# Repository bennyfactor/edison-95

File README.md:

HP 95LX Block for Intel Edison - Battery/Serial
=================================================

Based on the [SparkFun Block for Intel Edison - Battery/Power (DEV-13037)](https://www.sparkfun.com/products/13037)
and the reference design for the [MAX3218 low voltage TTL-RS232 transciever](https://datasheets.maximintegrated.com/en/ds/MAX3218.pdf)

This block or daughterboard, or whatever, is designed to fit in to the physical dimensions of the HP 95LX palmtop computer's
proto-PCMCIA slot. It has connections for two UARTs (the Edison's console out, and COM1?) that will allow either one to be connected to the HP95LX's serial header.
It also has the battery circuit for a lithium battery based on Sparkfun's design so that it can run on its own power while inside the palmtop!

Simply plug in a micro USB cable to charge.
The power switch removes the battery from the Edison while allowing it to charge via the microUSB cable.

Also fun LEDs for power status!

Repository Contents
-------------------
* **/hardware** - Eagle design files (.brd, .sch)

Documentation
--------------
* **[Hookup Guide](https://learn.sparkfun.com/tutorials/sparkfun-blocks-for-intel-edison---battery-block)** - Basic hookup guide for the SparkFun battery/power block.
* **[MAX3218 low voltage TTL-RS232 transciever](https://datasheets.maximintegrated.com/en/ds/MAX3218.pdf)** - Datasheet for the serial tranceiver.
* **[Intel Edison Hardware Guide](http://download.intel.com/support/edison/sb/edisonmodule_hg_331189004.pdf)** - Datasheet for the Edison module.

Sparkfun Product Versions
----------------
* [Battery Block](https://www.sparkfun.com/products/13037)- Battery block.
* [Power Block](https://www.sparkfun.com/products/13727)- Battery block without lipo battery installed.

License Information
-------------------

This product is _**open source**_!

Please review the LICENSE.md file for license information.

If you have any questions or concerns on licensing, please contact techsupport@sparkfun.com.

Distributed as-is; no warranty is given.

- Your friends at SparkFun. ALSO BENNY

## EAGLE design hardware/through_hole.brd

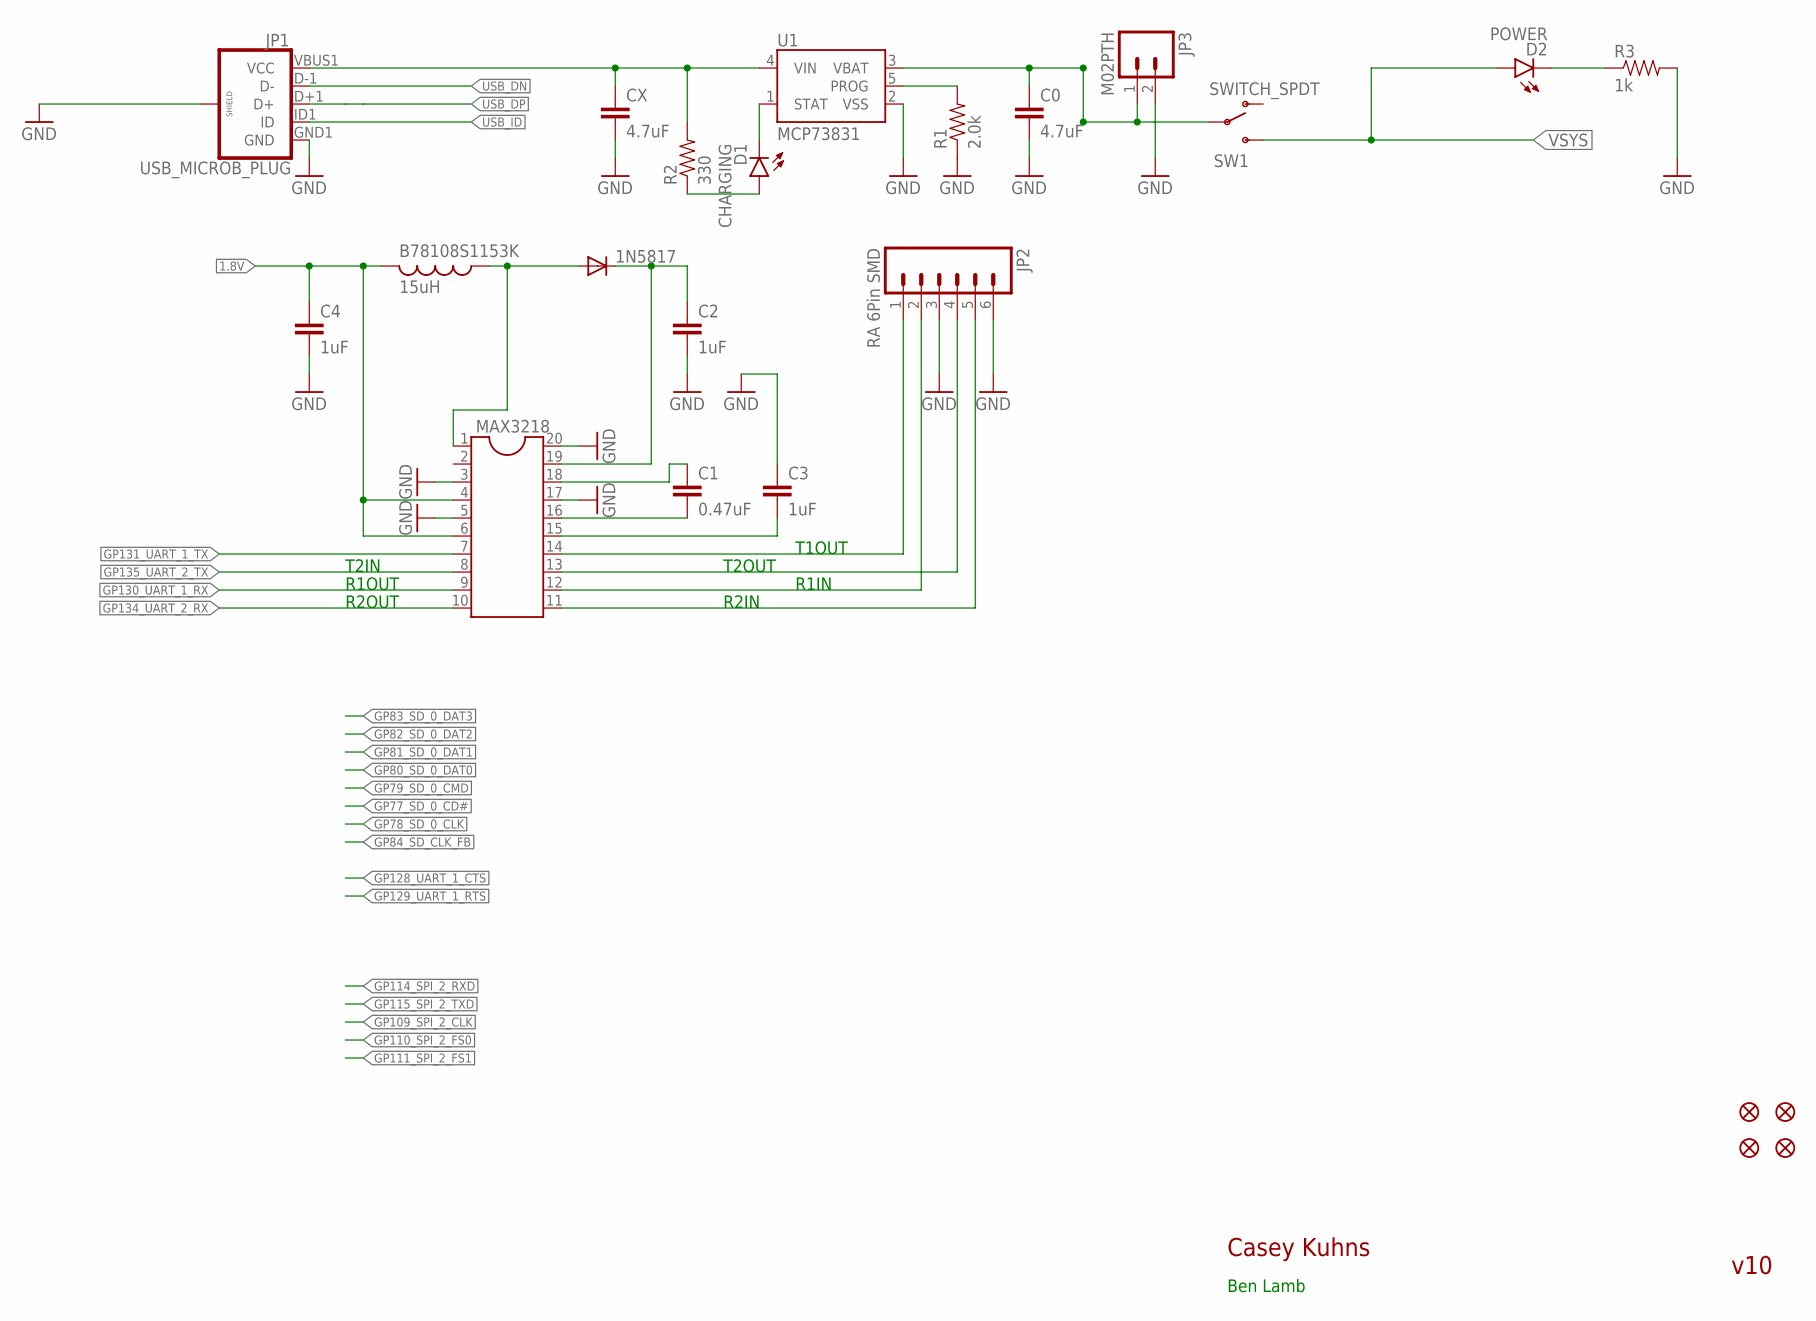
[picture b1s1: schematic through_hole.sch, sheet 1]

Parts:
1N5817: DIODE-DO41-10; DO41-10
B78108S1153K: 15uH; 0207/15
C0: 4.7uF; 0603-CAP
C1: 0.47uF; CAP-PTH-5MM
C2, C3, C4: 1uF; CAP-PTH-5MM
CX: 4.7uF; 0603-CAP
D1: CHARGING; LED-0603
D2: POWER; LED-0603
FID1, FID2, FID3, FID4: FIDUCIAL1X2; FIDUCIAL-1X2
JP1: USB_MICROB_PLUG; USB-B-MICRO-SMD_V03
JP2: RA 6Pin SMD; 1X06-SMD
JP3: M02PTH; 1X02
MAX3218: DIL20
R1: 2.0k; 0603-RES
R2: 330; 0603-RES
R3: 1k; 0603-RES
SW1: SWITCH_SPDT; KPS-1290
U1: MCP73831; SOT23-5

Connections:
1: 1N5817.A, B78108S1153K.1, MAX3218.1
1.8V: B78108S1153K.2, C4.1, MAX3218.4, MAX3218.6; also elsewhere on the board
CX: CX.1, JP1.VBUS1 (VCC), R2.2, U1.4 (VIN)
GND: C0.2, C2.2, C3.1, C4.2, CX.2, JP1.GND1 (GND), JP1.SHIELD1 (SHIELD), JP1.SHIELD2 (SHIELD), JP1.SHIELD3 (SHIELD), JP2.3, JP2.6, JP3.2, MAX3218.3, MAX3218.5, MAX3218.17, MAX3218.20, R1.1, R3.2, U1.2 (VSS); also elsewhere on the board
GP130_UART_1_RX: MAX3218.9; also elsewhere on the board
GP131_UART_1_TX: MAX3218.7; also elsewhere on the board
GP134_UART_2_RX: MAX3218.10; also elsewhere on the board
GP135_UART_2_TX: MAX3218.8; also elsewhere on the board
unnamed: D2.C, R3.1
unnamed: R1.2, U1.5 (PROG)
unnamed: D1.A, R2.1
unnamed: D1.C, U1.1 (STAT)
unnamed: C3.2, MAX3218.15
unnamed: C1.1, MAX3218.18
unnamed: C1.2, MAX3218.16
unnamed: JP2.4, MAX3218.13
unnamed: JP2.2, MAX3218.12
unnamed: JP2.5, MAX3218.11
unnamed: 1N5817.C, C2.1, MAX3218.19
T1OUT: JP2.1, MAX3218.14
USB_DN: JP1.D-1 (D-); also elsewhere on the board
USB_DP: JP1.D+1 (D+); also elsewhere on the board
USB_ID: JP1.ID1 (ID); also elsewhere on the board
VBAT: C0.1, JP3.1, SW1.P, U1.3 (VBAT)
VSYS: D2.A, SW1.S; also elsewhere on the board

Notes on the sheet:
Casey Kuhns
v10
R2IN
R1IN
T2OUT
T1OUT
T2IN
R1OUT
R2OUT
Ben Lamb

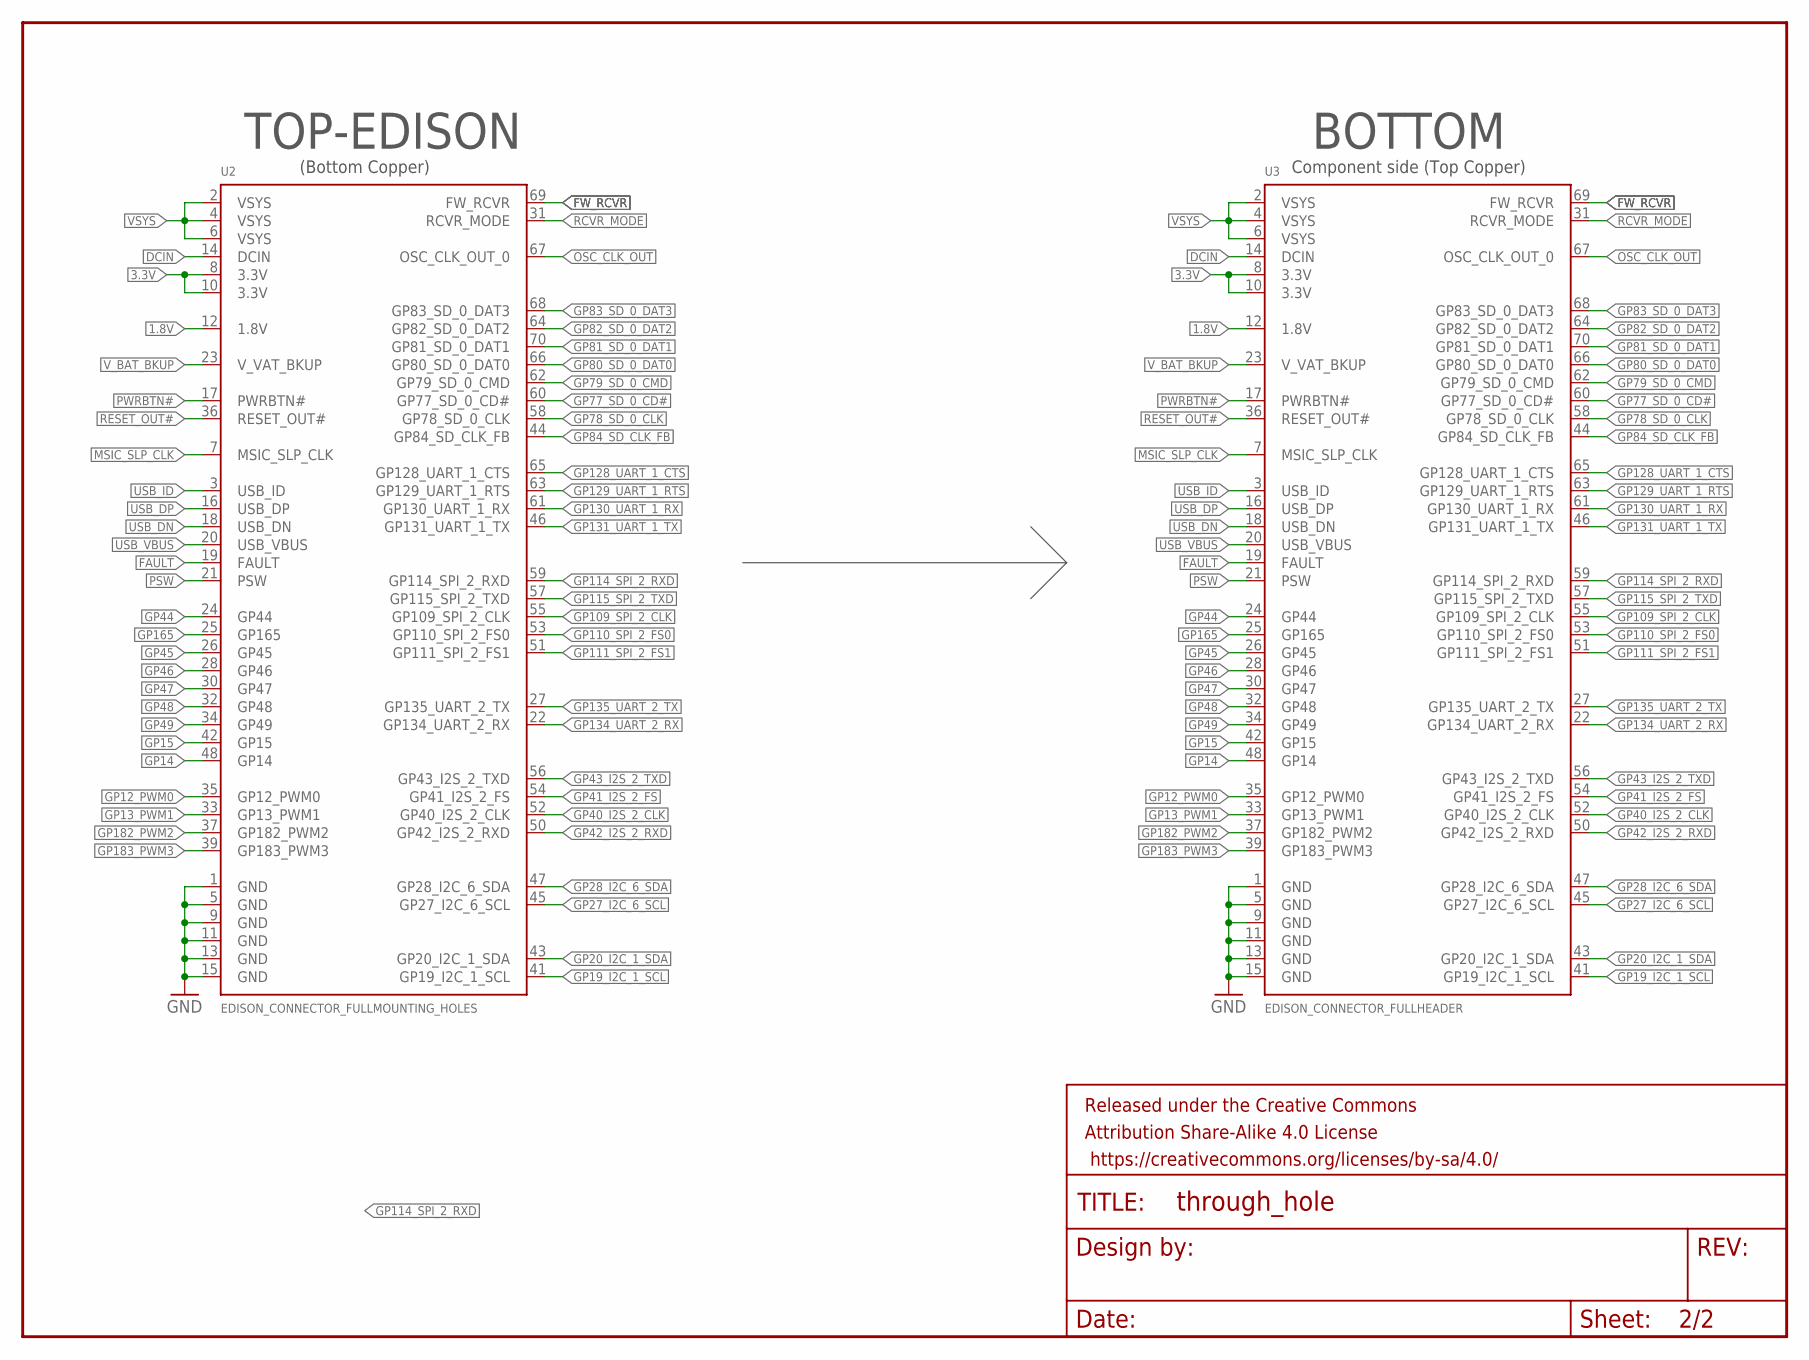
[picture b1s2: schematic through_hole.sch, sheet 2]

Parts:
FRAME2: FRAME-LETTER; CREATIVE_COMMONS
U2: EDISON_CONNECTOR_FULLMOUNTING_HOLES; EDISON_DAUGHTER
U3: EDISON_CONNECTOR_FULLHEADER; DF40C-70DP-0.4(51)

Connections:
1.8V: U2.12 (1.8V), U3.12 (1.8V); also elsewhere on the board
3.3V: U2.8 (3.3V), U2.10 (3.3V), U3.8 (3.3V), U3.10 (3.3V)
DCIN: U2.14 (DCIN), U3.14 (DCIN)
FAULT: U2.19 (FAULT), U3.19 (FAULT)
FW_RCVR: U2.69 (FW_RCVR), U3.69 (FW_RCVR)
GND: U2.1 (GND), U2.5 (GND), U2.9 (GND), U2.11 (GND), U2.13 (GND), U2.15 (GND), U3.1 (GND), U3.5 (GND), U3.9 (GND), U3.11 (GND), U3.13 (GND), U3.15 (GND); also elsewhere on the board
GP12_PWM0: U2.35 (GP12_PWM0), U3.35 (GP12_PWM0)
GP13_PWM1: U2.33 (GP13_PWM1), U3.33 (GP13_PWM1)
GP14: U2.48 (GP14), U3.48 (GP14)
GP15: U2.42 (GP15), U3.42 (GP15)
GP19_I2C_1_SCL: U2.41 (GP19_I2C_1_SCL), U3.41 (GP19_I2C_1_SCL)
GP20_I2C_1_SDA: U2.43 (GP20_I2C_1_SDA), U3.43 (GP20_I2C_1_SDA)
GP27_I2C_6_SCL: U2.45 (GP27_I2C_6_SCL), U3.45 (GP27_I2C_6_SCL)
GP28_I2C_6_SDA: U2.47 (GP28_I2C_6_SDA), U3.47 (GP28_I2C_6_SDA)
GP40_I2S_2_CLK: U2.52 (GP40_I2S_2_CLK), U3.52 (GP40_I2S_2_CLK)
GP41_I2S_2_FS: U2.54 (GP41_I2S_2_FS), U3.54 (GP41_I2S_2_FS)
GP42_I2S_2_RXD: U2.50 (GP42_I2S_2_RXD), U3.50 (GP42_I2S_2_RXD)
GP43_I2S_2_TXD: U2.56 (GP43_I2S_2_TXD), U3.56 (GP43_I2S_2_TXD)
GP44: U2.24 (GP44), U3.24 (GP44)
GP45: U2.26 (GP45), U3.26 (GP45)
GP46: U2.28 (GP46), U3.28 (GP46)
GP47: U2.30 (GP47), U3.30 (GP47)
GP48: U2.32 (GP48), U3.32 (GP48)
GP49: U2.34 (GP49), U3.34 (GP49)
GP77_SD_0_CD#: U2.60 (GP77_SD_0_CD#), U3.60 (GP77_SD_0_CD#)
GP78_SD_0_CLK: U2.58 (GP78_SD_0_CLK), U3.58 (GP78_SD_0_CLK)
GP79_SD_0_CMD: U2.62 (GP79_SD_0_CMD), U3.62 (GP79_SD_0_CMD)
GP80_SD_0_DAT0: U2.66 (GP80_SD_0_DAT0), U3.66 (GP80_SD_0_DAT0)
GP81_SD_0_DAT1: U2.70 (GP81_SD_0_DAT1), U3.70 (GP81_SD_0_DAT1)
GP82_SD_0_DAT2: U2.64 (GP82_SD_0_DAT2), U3.64 (GP82_SD_0_DAT2)
GP83_SD_0_DAT3: U2.68 (GP83_SD_0_DAT3), U3.68 (GP83_SD_0_DAT3)
GP84_SD_CLK_FB: U2.44 (GP84_SD_CLK_FB), U3.44 (GP84_SD_CLK_FB)
GP109_SPI_2_CLK: U2.55 (GP109_SPI_2_CLK), U3.55 (GP109_SPI_2_CLK)
GP110_SPI_2_FS0: U2.53 (GP110_SPI_2_FS0), U3.53 (GP110_SPI_2_FS0)
GP111_SPI_2_FS1: U2.51 (GP111_SPI_2_FS1), U3.51 (GP111_SPI_2_FS1)
GP114_SPI_2_RXD: U2.59 (GP114_SPI_2_RXD), U3.59 (GP114_SPI_2_RXD)
GP115_SPI_2_TXD: U2.57 (GP115_SPI_2_TXD), U3.57 (GP115_SPI_2_TXD)
GP128_UART_1_CTS: U2.65 (GP128_UART_1_CTS), U3.65 (GP128_UART_1_CTS)
GP129_UART_1_RTS: U2.63 (GP129_UART_1_RTS), U3.63 (GP129_UART_1_RTS)
GP130_UART_1_RX: U2.61 (GP130_UART_1_RX), U3.61 (GP130_UART_1_RX); also elsewhere on the board
GP131_UART_1_TX: U2.46 (GP131_UART_1_TX), U3.46 (GP131_UART_1_TX); also elsewhere on the board
GP134_UART_2_RX: U2.22 (GP134_UART_2_RX), U3.22 (GP134_UART_2_RX); also elsewhere on the board
GP135_UART_2_TX: U2.27 (GP135_UART_2_TX), U3.27 (GP135_UART_2_TX); also elsewhere on the board
GP165: U2.25 (GP165), U3.25 (GP165)
GP182_PWM2: U2.37 (GP182_PWM2), U3.37 (GP182_PWM2)
GP183_PWM3: U2.39 (GP183_PWM3), U3.39 (GP183_PWM3)
MSIC_SLP_CLK: U2.7 (MSIC_SLP_CLK), U3.7 (MSIC_SLP_CLK)
OSC_CLK_OUT: U2.67 (OSC_CLK_OUT_0), U3.67 (OSC_CLK_OUT_0)
PSW: U2.21 (PSW), U3.21 (PSW)
PWRBTN#: U2.17 (PWRBTN#), U3.17 (PWRBTN#)
RCVR_MODE: U2.31 (RCVR_MODE), U3.31 (RCVR_MODE)
RESET_OUT#: U2.36 (RESET_OUT#), U3.36 (RESET_OUT#)
USB_DN: U2.18 (USB_DN), U3.18 (USB_DN); also elsewhere on the board
USB_DP: U2.16 (USB_DP), U3.16 (USB_DP); also elsewhere on the board
USB_ID: U2.3 (USB_ID), U3.3 (USB_ID); also elsewhere on the board
USB_VBUS: U2.20 (USB_VBUS), U3.20 (USB_VBUS)
VSYS: U2.2 (VSYS), U2.4 (VSYS), U2.6 (VSYS), U3.2 (VSYS), U3.4 (VSYS), U3.6 (VSYS); also elsewhere on the board
V_BAT_BKUP: U2.23 (V_VAT_BKUP), U3.23 (V_VAT_BKUP)

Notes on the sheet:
TOP-EDISON
BOTTOM
Component side (Top Copper)
(Bottom Copper)

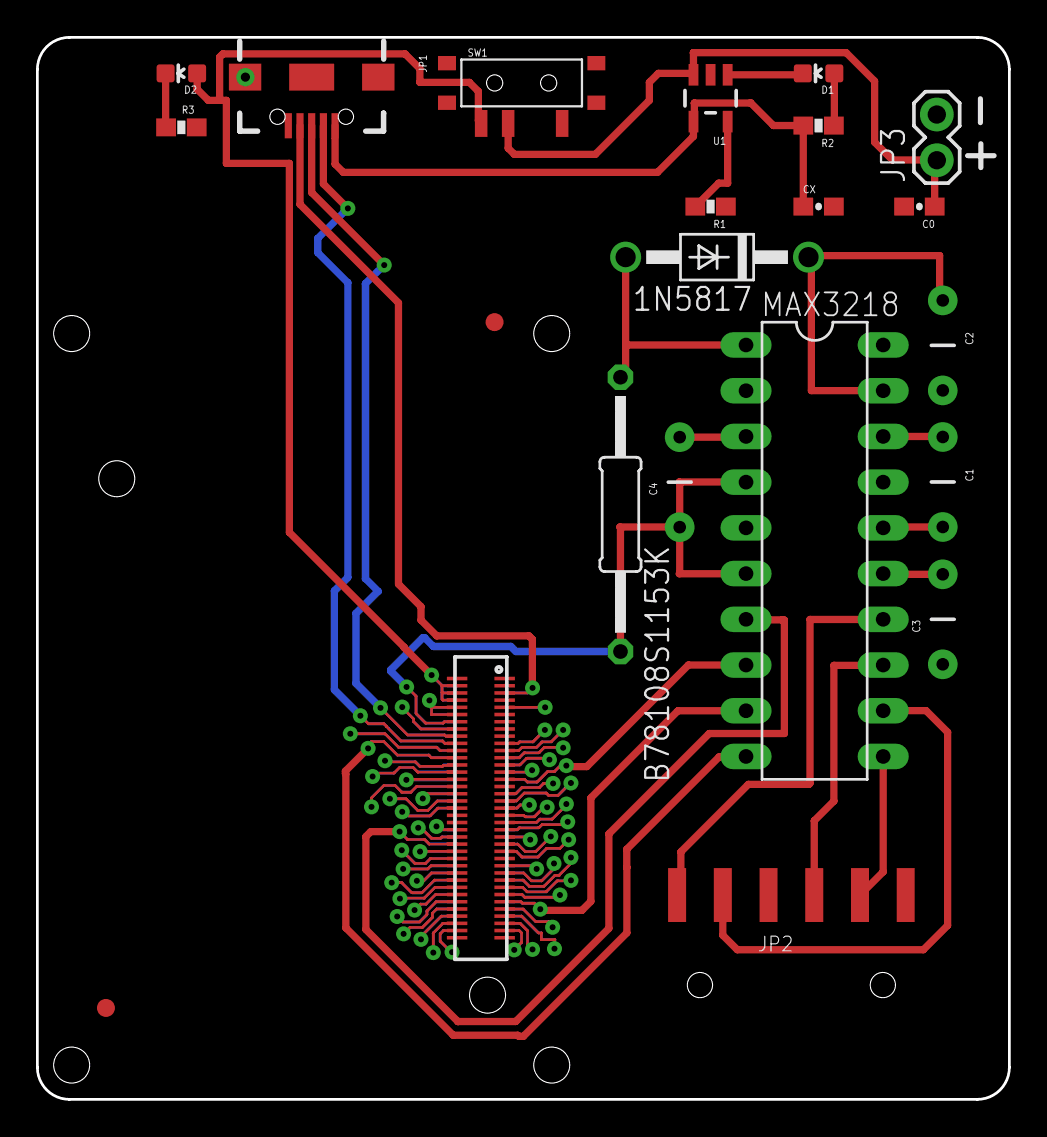
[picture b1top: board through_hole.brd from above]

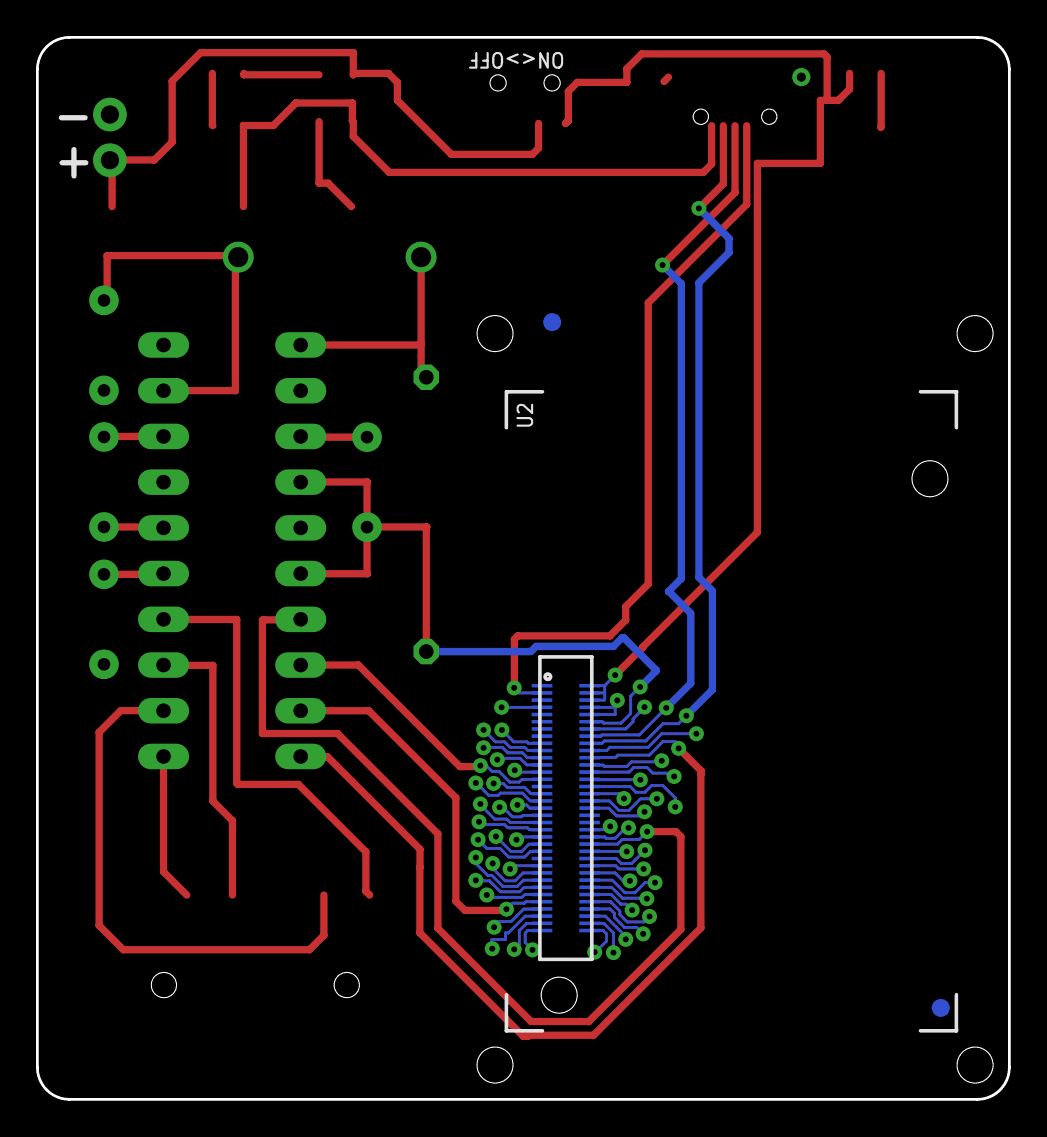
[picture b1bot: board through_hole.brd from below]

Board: 2 copper layers, 54.0 x 59.0 mm, 26 parts (4 on the bottom side), 73 nets.

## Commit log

2015-10-07 initial commit as board for HP95LX
2015-10-07 Initial HP95LX daughterboard layouts
2015-10-07 add USB data lines, use 1.8v line, not vcc, for Max3218, DRC fixes
2015-10-10 Update readme, board routing fixes, change LED names to functions vice colors
2015-10-14 add version with through hole transistors for ease of soldering
2015-10-14 Add BOM for thru hole board

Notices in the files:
parts and their libraries:
SparkFun-Aesthetics: Licensing: Creative Commons ShareAlike 4.0 International - https://creativecommons.org/licenses/by-sa/4.0
SparkFun-Aesthetics: Released under the Creative Commons Attribution Share-Alike 4.0 License
SparkFun-Aesthetics: https://creativecommons.org/licenses/by-sa/4.0
